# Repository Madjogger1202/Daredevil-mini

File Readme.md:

# Daredevil-mini

> USB MEMS microphone module with four selectable sensors on one board.  
> **Sensors:** INMP441 • MP34DT01 • SPH0645LM4 • MP23DB01.  
> Each sensor wired individually to **RP2040** core.  
> Form factor: **USB stick** (direct plug-in).  

---

## What’s on the board
- **Four MEMS microphones** for direct comparison:
  - INMP441  
  - MP34DT01  
  - SPH0645LM4  
  - MP23DB01
- All connected separately to **RP2040**  
  *(see schematic for detailed pinout)*
- **Two groups of LEDs**:
  - 2× status LEDs (power / activity)  
  - 4× level LEDs (visualize audio from active sensor)
- **BOOT button** for easy programming (UF2 bootloader compatible)
- Component layout matches **Raspberry Pi Pico** (same footprints / values for cost-reduction & rework flexibility)

---

## Power & Form Factor
- Powered directly from **USB-A plug**  
- Compact **flash-drive-style** PCB — just insert into USB port  
- No external power required

---

## Use Case
- Quick **A/B/C/D comparison** of MEMS microphones  
- Evaluate noise, sensitivity, frequency response, clipping  
- Decide on best sensor for a given project (voice, audio capture, beamforming, etc.)

---

## Quick Use
1. Plug **Daredevil-mini** into USB port.  
2. Hold **BOOT** and connect to enter RP2040 bootloader.  
3. Flash your firmware (UF2 or via SWD if needed).  
4. Select and test microphones, use LED bar as quick visual feedback.  
5. Log / stream audio over USB or I²S as defined in firmware.

---

## Notes
- Do not use multiple sensors at the same time (shared core, for comparison only).  
- Pin mapping for each microphone: **see schematic**.  
- Board re-buildable using **Pi Pico BOM** (same package sizes).  

---

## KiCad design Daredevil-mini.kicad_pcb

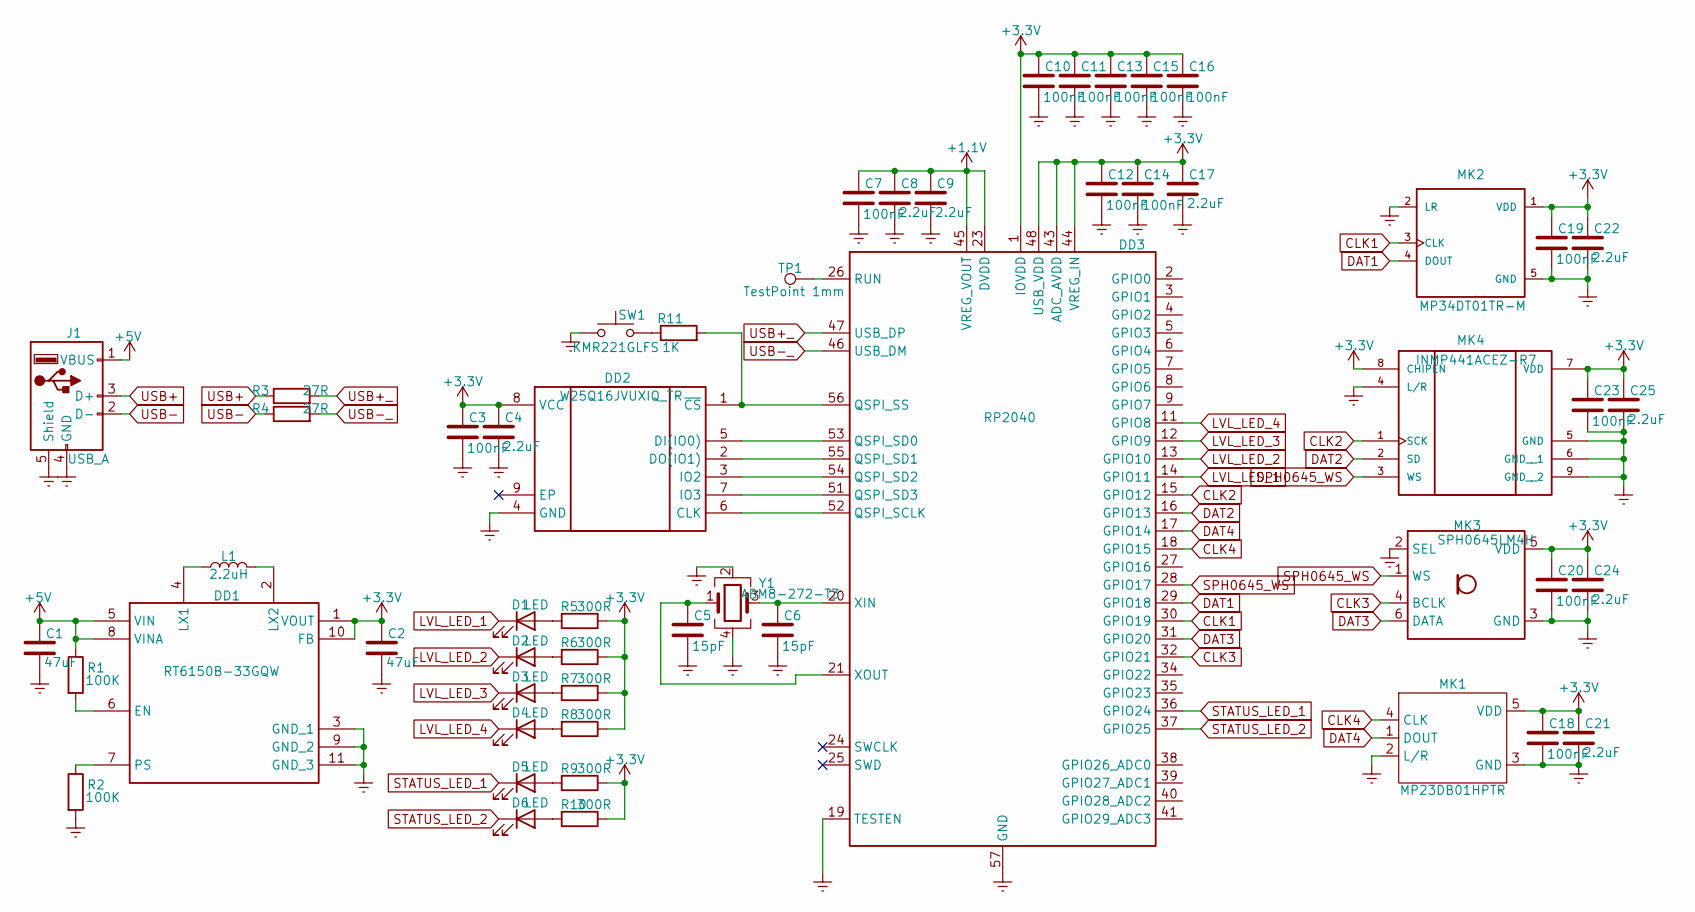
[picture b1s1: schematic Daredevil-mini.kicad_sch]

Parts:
C1, C2: 47uF; C_0805_2012Metric
C3, C7, C10, C11, C12, C13, C14, C15, C16, C18, C19, C20, C23: 100nF; C_0201_0603Metric
C4, C8, C9, C17, C21, C22, C24, C25: 2.2uF; C_0402_1005Metric
C5, C6: 15pF; C_0201_0603Metric
D1, D2, D3, D4, D5, D6: LED; LED_0402_1005Metric
DD1: RT6150B-33GQW; Manufacturer_Part_Number RT6150B-33GQW; Mouser Part Number 835-RT6150B-33GQW
DD2: W25Q16JVUXIQ_TR; W25Q16JVUXIQ; Manufacturer_Part_Number W25Q16JVUXIQ TR; Mouser Part Number 454-W25Q16JVUXIQTR
DD3: RP2040; QFN-56-1EP_7x7mm_P0.4mm_EP3.2x3.2mm
J1: USB_A; USB_A_Connfly_DS1098_Horizontal
L1: 2.2uH; L_1008_2520Metric
MK1: MP23DB01HPTR; Manufacturer Part MP23DB01HPTR; LCSC Part Name MP23DB01HPTR
MK2: MP34DT01TR-M; MP34DT01; MPN MP34DT01TR-M
MK3: SPH0645LM4H; Knowles_SPH0645LM4H-6_3.5x2.65mm
MK4: INMP441ACEZ-R7; INMP441; PARTREV 1.1
R1, R2: 100K; R_0402_1005Metric
R3, R4: 27R; R_0201_0603Metric
R5, R6, R7, R8, R9, R10: 300R; R_0402_1005Metric
R11: 1K; R_0402_1005Metric
SW1: KMR221GLFS; SW_SPST_PTS810
TP1: TestPoint 1mm; TestPoint_Pad_D1.0mm
Y1: ABM8-272-T3; Crystal_SMD_3225-4Pin_3.2x2.5mm

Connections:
+1.1V: C7.1, C8.1, C9.1, DD3.23 (DVDD), DD3.45 (VREG_VOUT), DD3.50 (DVDD)
+3.3V: C2.1, C3.1, C4.1, C10.1, C11.1, C12.1, C13.1, C14.1, C15.1, C16.1, C17.1, C18.1, C19.1, C20.1, C21.1, C22.1, C23.1, C24.1, C25.1, DD1.1 (VOUT), DD1.10 (FB), DD2.8 (VCC), DD3.1 (IOVDD), DD3.10 (IOVDD), DD3.22 (IOVDD), DD3.33 (IOVDD), DD3.42 (IOVDD), DD3.43 (ADC_AVDD), DD3.44 (VREG_IN), DD3.48 (USB_VDD), DD3.49 (IOVDD), MK1.5 (VDD), MK2.1 (VDD), MK3.5 (VDD), MK4.7 (VDD), MK4.8 (CHIPEN), R5.1, R6.1, R7.1, R8.1, R9.1, R10.1
+5V: C1.1, DD1.5 (VIN), DD1.8 (VINA), J1.1 (VBUS), R1.1
CLK1: DD3.30 (GPIO19), MK2.3 (CLK)
CLK2: DD3.15 (GPIO12), MK4.1 (SCK)
CLK3: DD3.32 (GPIO21), MK3.4 (BCLK)
CLK4: DD3.18 (GPIO15), MK1.4 (CLK)
DAT1: DD3.29 (GPIO18), MK2.4 (DOUT)
DAT2: DD3.16 (GPIO13), MK4.2 (SD)
DAT3: DD3.31 (GPIO20), MK3.6 (DATA)
DAT4: DD3.17 (GPIO14), MK1.1 (DOUT)
Earth: C1.2, C2.2, C3.2, C4.2, C5.2, C6.2, C7.2, C8.2, C9.2, C10.2, C11.2, C12.2, C13.2, C14.2, C15.2, C16.2, C17.2, C18.2, C19.2, C20.2, C21.2, C22.2, C23.2, C24.2, C25.2, DD1.3 (GND_1), DD1.9 (GND_2), DD1.11 (GND_3), DD2.4 (GND), DD3.19 (TESTEN), DD3.57 (GND), J1.4 (GND), J1.5 (Shield), MK1.2 (L/R), MK1.3 (GND), MK2.2 (LR), MK2.5 (GND), MK3.2 (SEL), MK3.3 (GND), MK4.4 (L/R), MK4.5 (GND), MK4.6 (GND__1), MK4.9 (GND__2), R2.2, SW1.1, Y1.2, Y1.4
LVL_LED_1: D1.1 (K), DD3.14 (GPIO11)
LVL_LED_2: D2.1 (K), DD3.13 (GPIO10)
LVL_LED_3: D3.1 (K), DD3.12 (GPIO9)
LVL_LED_4: D4.1 (K), DD3.11 (GPIO8)
unnamed: D1.2 (A), R5.2
unnamed: D2.2 (A), R6.2
unnamed: D3.2 (A), R7.2
unnamed: D4.2 (A), R8.2
unnamed: D5.2 (A), R9.2
unnamed: D6.2 (A), R10.2
unnamed: DD1.6 (EN), R1.2
unnamed: DD1.4 (LX1), L1.1
unnamed: DD1.2 (LX2), L1.2
unnamed: DD1.7 (PS), R2.1
unnamed: DD2.6 (CLK), DD3.52 (QSPI_SCLK)
unnamed: DD2.5 (DI(IO0)), DD3.53 (QSPI_SD0)
unnamed: DD2.2 (DO(IO1)), DD3.55 (QSPI_SD1)
unnamed: DD2.3 (IO2), DD3.54 (QSPI_SD2)
unnamed: DD2.7 (IO3), DD3.51 (QSPI_SD3)
unnamed: DD2.1 (~CS), DD3.56 (QSPI_SS), R11.2
unnamed: DD3.26 (RUN), TP1.1
unnamed: C6.1, DD3.20 (XIN), Y1.3
unnamed: C5.1, DD3.21 (XOUT), Y1.1
unnamed: R11.1, SW1.2
SPH0645_WS: DD3.28 (GPIO17), MK3.1 (WS), MK4.3 (WS)
STATUS_LED_1: D5.1 (K), DD3.36 (GPIO24)
STATUS_LED_2: D6.1 (K), DD3.37 (GPIO25)
USB+: J1.3 (D+), R3.1
USB+_: DD3.47 (USB_DP), R3.2
USB-: J1.2 (D-), R4.1
USB-_: DD3.46 (USB_DM), R4.2

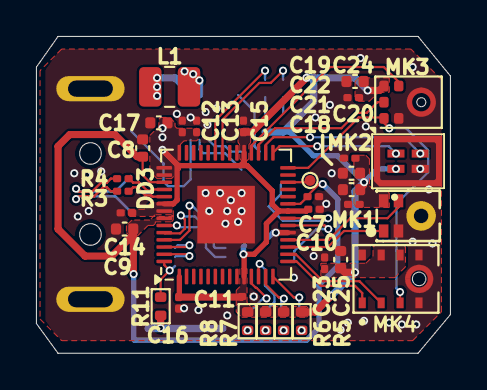
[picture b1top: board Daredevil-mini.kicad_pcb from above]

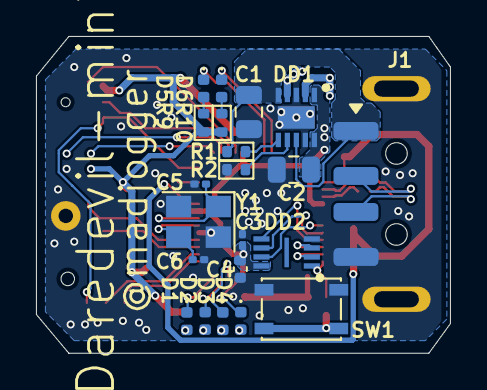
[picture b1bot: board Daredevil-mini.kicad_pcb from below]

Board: 2 copper layers, 23.0 x 17.6 mm, 54 parts (21 on the bottom side), 43 nets.

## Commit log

2025-08-24 Schematics done, all 3D models in places and imported all components on PCB, ready to work on PCB
2025-08-25 udp PCB
2025-08-25 rev0 ready
